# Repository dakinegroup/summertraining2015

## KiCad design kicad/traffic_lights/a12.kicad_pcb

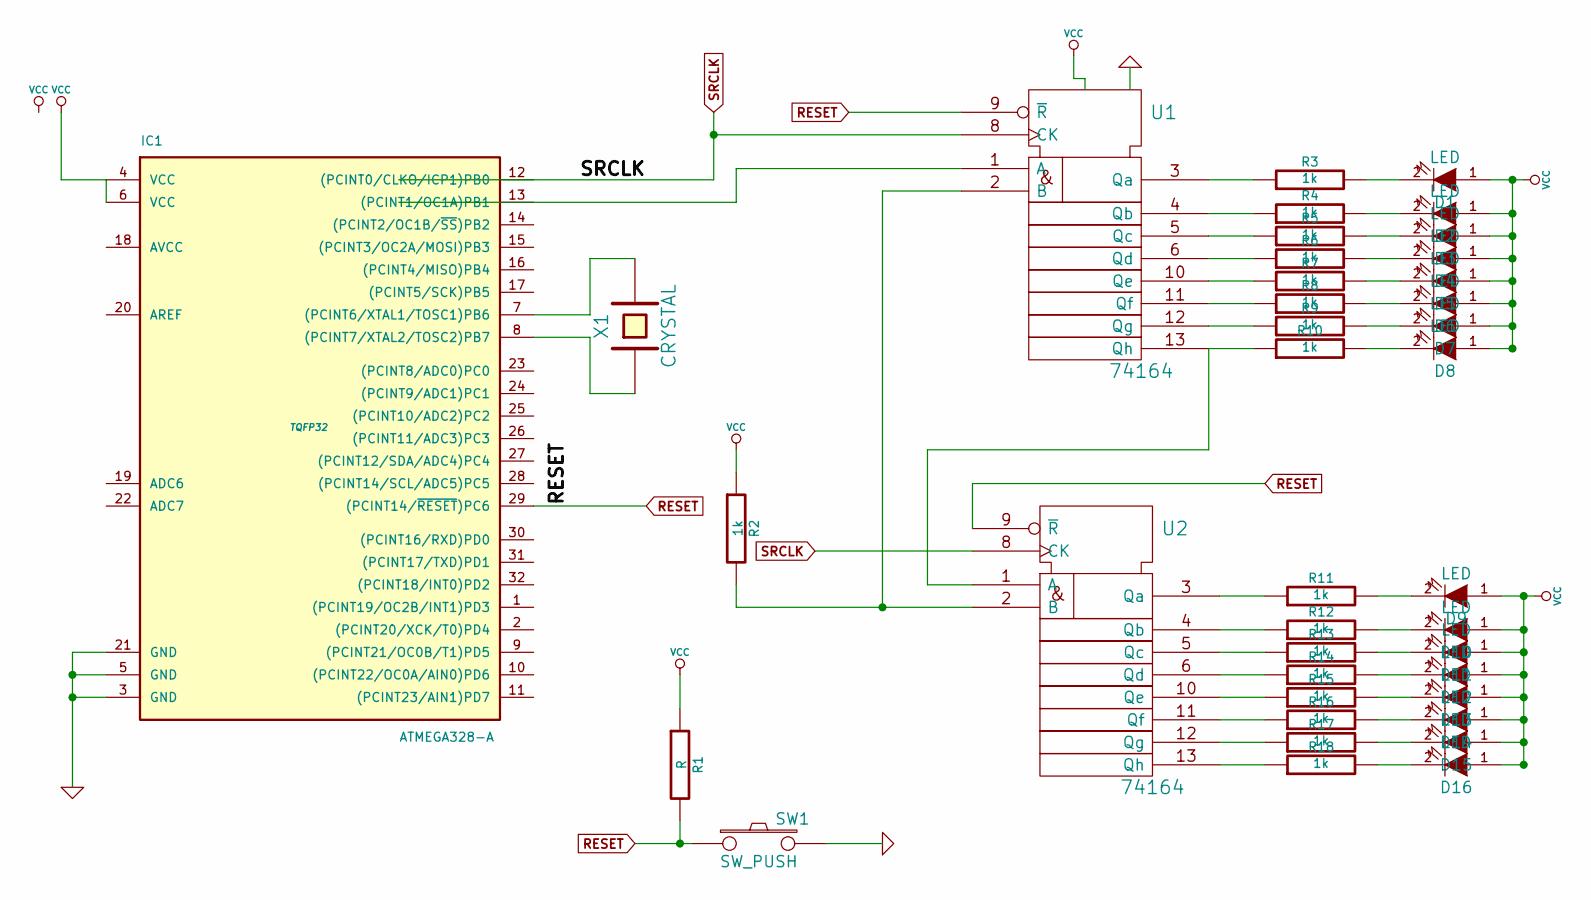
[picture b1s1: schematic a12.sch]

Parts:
D1, D2, D3, D4, D5, D6, D7, D8, D9, D10, D11, D12, D13, D14, D15, D16: LED
IC1: ATMEGA328-A; TQFP32
R1: R
R2, R3, R4, R5, R6, R7, R8, R9, R10, R11, R12, R13, R14, R15, R16, R17, R18: 1k
SW1: SW_PUSH
U1, U2: 74164
X1: CRYSTAL

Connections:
GND: IC1.3 (GND), IC1.5 (GND), IC1.21 (GND), SW1.2, U1.14 (Vdd), U2.14 (Vdd)
unnamed: D5.2 (K), R7.2
unnamed: R8.1, U1.11 (Qf)
unnamed: D6.2 (K), R8.2
unnamed: R7.1, U1.10 (Qe)
unnamed: D4.2 (K), R6.2
unnamed: R6.1, U1.6 (Qd)
unnamed: D3.2 (K), R5.2
unnamed: D8.2 (K), R10.2
unnamed: D11.2 (K), R13.2
unnamed: R13.1, U2.5 (Qc)
unnamed: D10.2 (K), R12.2
unnamed: R12.1, U2.4 (Qb)
unnamed: D9.2 (K), R11.2
unnamed: R11.1, U2.3 (Qa)
unnamed: R5.1, U1.5 (Qc)
unnamed: D7.2 (K), R9.2
unnamed: R9.1, U1.12 (Qg)
unnamed: D2.2 (K), R4.2
unnamed: R4.1, U1.4 (Qb)
unnamed: D1.2 (K), R3.2
unnamed: R3.1, U1.3 (Qa)
unnamed: R10.1, U1.13 (Qh), U2.1 (A)
unnamed: IC1.8 ((PCINT7/XTAL2/TOSC2)PB7), X1.1
unnamed: IC1.7 ((PCINT6/XTAL1/TOSC1)PB6), X1.2
unnamed: R2.2, U1.2 (B), U2.2 (B)
unnamed: D14.2 (K), R16.2
unnamed: R16.1, U2.11 (Qf)
unnamed: D13.2 (K), R15.2
unnamed: R15.1, U2.10 (Qe)
unnamed: D12.2 (K), R14.2
unnamed: R14.1, U2.6 (Qd)
unnamed: D16.2 (K), R18.2
unnamed: R18.1, U2.13 (Qh)
unnamed: D15.2 (K), R17.2
unnamed: R17.1, U2.12 (Qg)
RESET: IC1.29 ((PCINT14/~RESET~)PC6), R1.2, SW1.1, U1.9 (~R), U2.9 (~R)
SRCLK: U1.8 (CK), U2.8 (CK)
VCC: D1.1 (A), D2.1 (A), D3.1 (A), D4.1 (A), D5.1 (A), D6.1 (A), D7.1 (A), D8.1 (A), D9.1 (A), D10.1 (A), D11.1 (A), D12.1 (A), D13.1 (A), D14.1 (A), D15.1 (A), D16.1 (A), IC1.4 (VCC), IC1.6 (VCC), R1.1, R2.1, U1.7 (Vss), U2.7 (Vss)

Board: 2 copper layers, 39 parts (0 on the bottom side), 39 nets, no tracks yet.

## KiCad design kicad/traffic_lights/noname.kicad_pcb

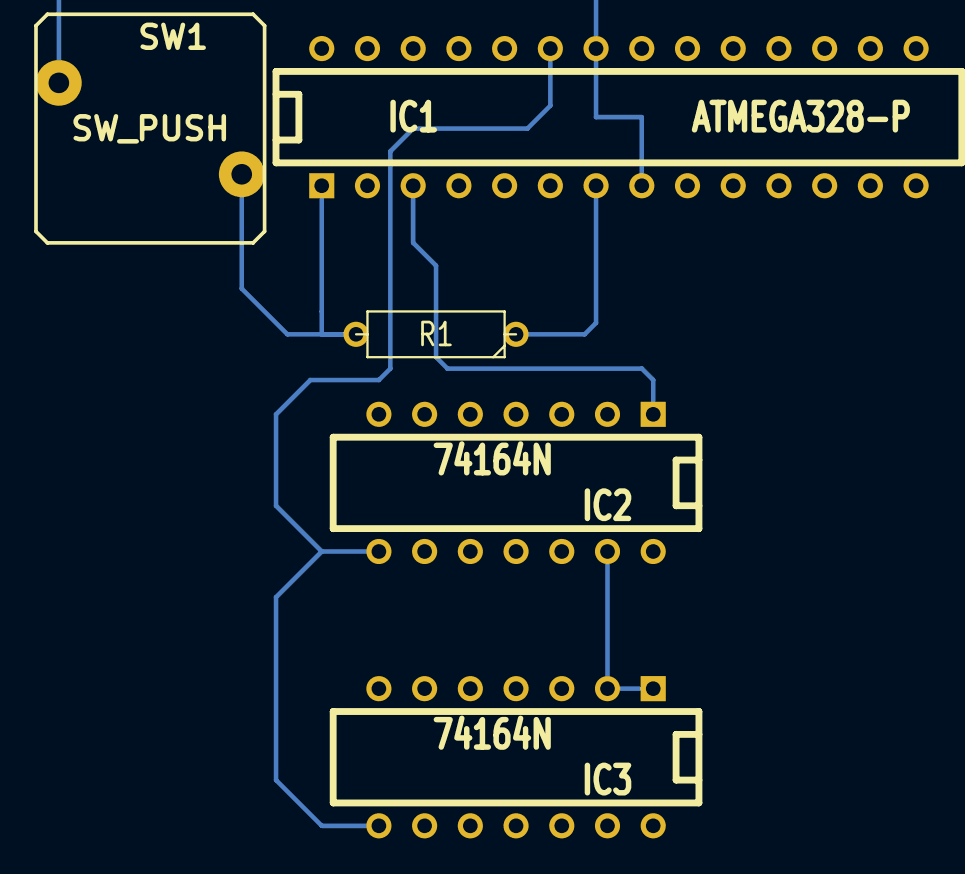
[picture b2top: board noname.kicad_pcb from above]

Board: 2 copper layers, 5 parts (0 on the bottom side), 6 nets.

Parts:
IC1: ATMEGA328-P; DIP-28__300
IC2, IC3: 74164N; DIP-14__300
R1: R; R3-5
SW1: SW_PUSH

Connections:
GND: IC1.8, IC1.22, SW1.1
unnamed: IC2.13, IC3.1, IC3.2
unnamed: IC1.3, IC2.1, IC2.2
RESET_L: IC1.1, R1.2, SW1.2
SR_CLK: IC1.23, IC2.8, IC3.8
VCC: IC1.7, R1.1

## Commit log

2015-05-20 added tasks
2015-05-20 added guidelines..
2015-05-26 updated..
2015-05-27 updates..
2015-05-27 added to reports..
2015-05-27 moved report documentation to report directory
2015-05-27 renamed files..
2015-05-27 ignored added..
2015-05-27 added project report..
2015-05-29 updated bom
2015-05-29 updated learning atmega..
2015-05-30 update..
2015-05-30 udpates..
2015-05-30 update for learning..
2015-06-01 updates for traffic lights code
2015-06-01 y abh ^x ^X -m "abc"
2015-06-01 circuit stage images
2015-06-01 added images
2015-06-01 updates for images
2015-06-04 Create gh-pages branch via GitHub
2015-06-05 renamed files
2015-06-05 added cad files
2015-06-08 added atmega diagram
2015-06-15 counter
2015-06-16 renamed file
2015-06-16 reviwed learning vlsi
2015-06-16 moore's law
2015-06-16 creating final project
2015-06-16 trblshoot updated, written tx int routing
2015-06-16 ISR still failing to get kicked off
2015-06-17 interrupts now working.. but still unable to send data through interrupt SR
2015-06-17 interrupts enabled, rx data working..
2015-06-17 second time input not received.. alternatively working
2015-06-17 counter'll b completed by tomorrow
2015-06-17 changed hardware for PORTD3 to portd2
2015-06-17 fixed crash issue..
2015-06-18 added schema drawing
2015-06-19 usart int working
2015-06-19 working isr
2015-06-19 did it
2015-06-19 organized code into components
2015-06-19 minor compile fix
2015-06-19 initiated framework
2015-06-20 renamed directories ..
2015-06-20 renamed..
2015-06-20 updated demo pwm file
2015-06-20 renamed to task
2015-06-20 renamed
2015-06-20 adding lcd skelton
2015-06-20 added doc for circuit cable connections
2015-06-20 lcd start code
2015-06-22 final LCD
2015-06-22 integ tl
2015-06-23 update report
2015-06-23 minor chg to trblshoot
2015-06-23 added ext interrupts code
2015-06-23 removed .o files
2015-06-24 minor fix..
2015-06-24 now working trfc counters..
2015-06-24 remaining stuff
2015-06-24 report update
2015-06-24 added schematic
2015-06-24 added circuit images
2015-06-24 added bom
2015-06-25 report updated..
2015-06-25 tc_main.jpg added
2015-06-25 update lcd ckt
2015-06-25 adc added
2015-06-25 added tr led lcd stat
2015-06-25 task 11 for adc testing..
2015-06-26 fix hang issue
2015-06-26 fix for traffic counters
2015-06-26 added..
2015-06-26 reort update
2015-06-26 .
    .
2015-06-26 prj rpt
    prj rpt
2015-06-29 reviewed report - 1
